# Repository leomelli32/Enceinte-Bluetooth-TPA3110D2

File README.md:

# Enceinte-Bluetooth-TPA3110D2
Conception d'une enceinte Bluetooth avec un amplificateur TPA3110D2 et un récepteur Bluetooth MH-M18.

## Caractéristiques techniques
- **Amplificateur :** Amplificateur TPA3110D2 de classe D (puissance de 2x15W limité à 8 pour les hauts-parleurs en stéréo)
- **Hauts parleurs :** Hauts parleurs d'une JBL Flip 3 (impédance d'entrée : 4 Ohms; puisance : 8 W)
- **Connectivité :** Récepteur Bluetooth MH-M18 géré par un diviseur de tension
- **Alimentation :** Pack Lithium-ion 3S (11.1V nominal) avec protection BMS et recharge USB-C via OT8228

## Paramétrages
- **Limitation de puissance :** Fonction PLIMIT de l'amplificateur, tension fixée à 2,19 V
- **Gain :** réglé à valeur minimale de 20 dB
- **Filtrage :** Filtre LC de sortie (15µH / 2.2µF) avec fréquence de coupure à 27 kHz.
- **PCB :** 4 couches : 1,2,4: GND; 3: Alimentation 12 V

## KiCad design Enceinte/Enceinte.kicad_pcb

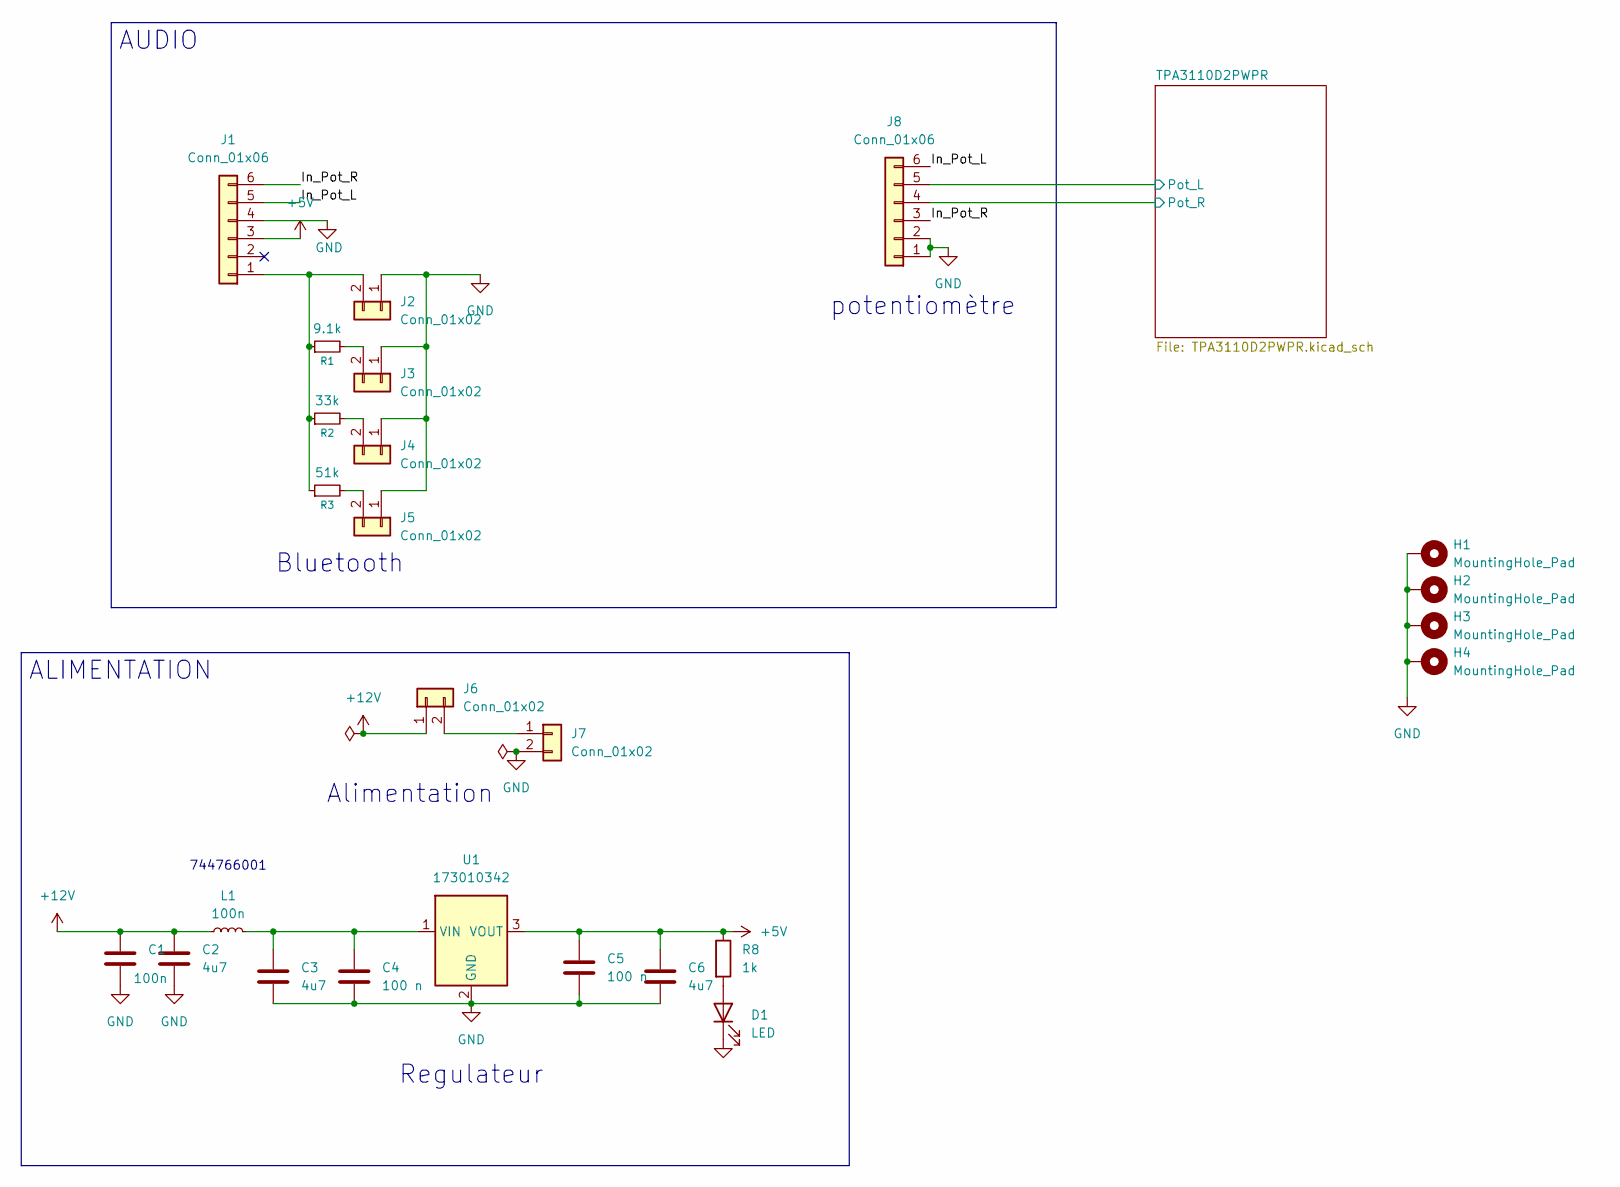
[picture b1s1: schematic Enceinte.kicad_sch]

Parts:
C1: 100n; C_0603_1608Metric
C2, C3, C6: 4u7; C_0603_1608Metric
C4, C5: 100 n; C_0603_1608Metric
D1: LED; LED_0603_1608Metric
H1, H2, H3, H4: MountingHole_Pad; MountingHole_2.5mm_Pad
J1, J8: Conn_01x06; JST_XH_B6B-XH-A_1x06_P2.50mm_Vertical
J2, J3, J4, J5, J6, J7: Conn_01x02; JST_XH_B2B-XH-A_1x02_P2.50mm_Vertical
L1: 100n; L_Wuerth_HCI-5040
R1: 9.1k; R_0603_1608Metric
R2: 33k; R_0603_1608Metric
R3: 51k; R_0603_1608Metric_Pad0.98x0.95mm_HandSolder
R8: 1k; R_0402_1005Metric
U1: 173010342; U_Wurth_MagIC-FDSM_173010x42

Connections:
+5V: C5.1, C6.1, J1.3, R8.1, U1.3 (VOUT)
+12V: C1.2, C2.1, J6.1, L1.1; also elsewhere on the board
/In_Pot_L: J1.5, J8.6
/In_Pot_R: J1.6, J8.3
/TPA3110D2PWPR/Pot_L: J8.5; also elsewhere on the board
/TPA3110D2PWPR/Pot_R: J8.4; also elsewhere on the board
GND: C1.1, C2.2, C3.2, C4.2, C5.2, C6.2, D1.1 (K), H1.1, H2.1, H3.1, H4.1, J1.4, J2.1, J3.1, J4.1, J5.1, J7.2, J8.1, J8.2, U1.2 (GND); also elsewhere on the board
unnamed: D1.2 (A), R8.2
unnamed: J1.1, J2.2, R1.1, R2.1, R3.1
unnamed: J3.2, R1.2
unnamed: J4.2, R2.2
unnamed: J5.2, R3.2
unnamed: J6.2, J7.1
unnamed: C3.1, C4.1, L1.2, U1.1 (VIN)

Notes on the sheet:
Regulateur
Alimentation
potentiomètre
Bluetooth
744766001
AUDIO
ALIMENTATION

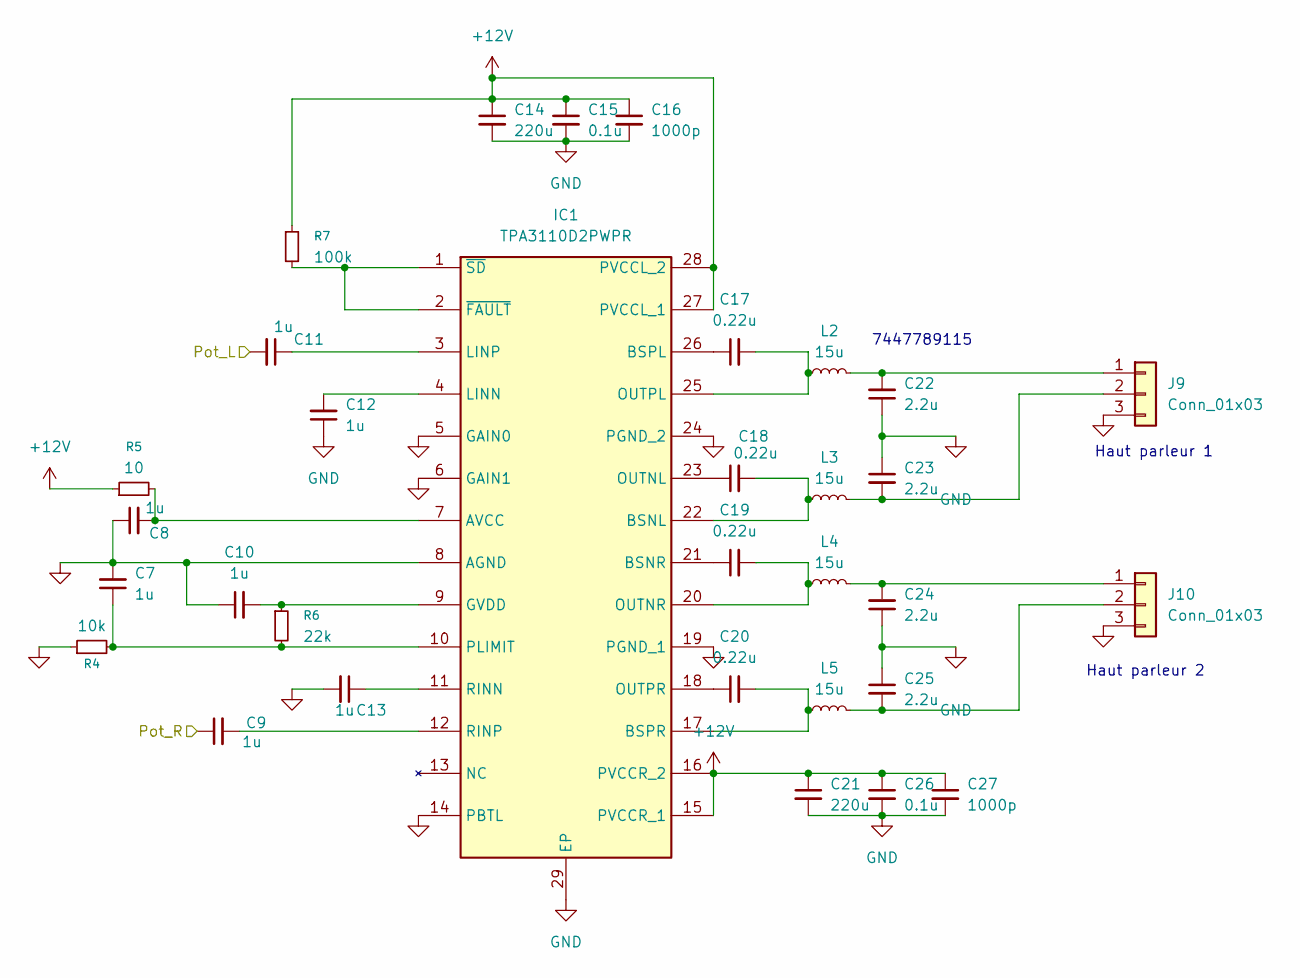
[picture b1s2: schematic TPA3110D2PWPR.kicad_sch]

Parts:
C7, C8, C9, C10, C11, C12, C13: 1u; C_0603_1608Metric
C14, C21: 220u; CP_Elec_6.3x7.7
C15, C26: 0.1u; C_0603_1608Metric
C16, C27: 1000p; C_0603_1608Metric
C17, C18, C19, C20: 0.22u; C_0603_1608Metric
C22, C23, C24, C25: 2.2u; C_0603_1608Metric
IC1: TPA3110D2PWPR; SOP65P640X120-29N; Mouser Part Number 595-TPA3110D2PWPR
J9, J10: Conn_01x03; JST_XH_B3B-XH-A_1x03_P2.50mm_Vertical
L2, L3, L4, L5: 15u; L_Wuerth_WE-PD-Typ-7345
R4: 10k; R_0603_1608Metric
R5: 10; R_0603_1608Metric
R6: 22k; R_0603_1608Metric
R7: 100k; R_0603_1608Metric

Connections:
+12V: C14.1, C15.1, C16.1, C21.1, C26.1, C27.1, IC1.15 (PVCCR_1), IC1.16 (PVCCR_2), IC1.27 (PVCCL_1), IC1.28 (PVCCL_2), R5.1, R7.1; also elsewhere on the board
/TPA3110D2PWPR/Pot_L: C11.2; also elsewhere on the board
/TPA3110D2PWPR/Pot_R: C9.1; also elsewhere on the board
GND: C7.2, C8.1, C10.1, C12.1, C13.2, C14.2, C15.2, C16.2, C21.2, C22.1, C23.1, C24.1, C25.1, C26.2, C27.2, IC1.5 (GAIN0), IC1.6 (GAIN1), IC1.8 (AGND), IC1.14 (PBTL), IC1.19 (PGND_1), IC1.24 (PGND_2), IC1.29 (EP), J9.3, J10.3, R4.1; also elsewhere on the board
unnamed: C8.2, IC1.7 (AVCC), R5.2
unnamed: C18.2, IC1.22 (BSNL), L3.1
unnamed: C19.1, IC1.21 (BSNR)
unnamed: C17.1, IC1.26 (BSPL)
unnamed: C20.2, IC1.17 (BSPR), L5.1
unnamed: C10.2, IC1.9 (GVDD), R6.1
unnamed: C12.2, IC1.4 (LINN)
unnamed: C11.1, IC1.3 (LINP)
unnamed: C18.1, IC1.23 (OUTNL)
unnamed: C19.2, IC1.20 (OUTNR), L4.1
unnamed: C17.2, IC1.25 (OUTPL), L2.1
unnamed: C20.1, IC1.18 (OUTPR)
unnamed: C7.1, IC1.10 (PLIMIT), R4.2, R6.2
unnamed: C13.1, IC1.11 (RINN)
unnamed: C9.2, IC1.12 (RINP)
unnamed: IC1.1 (~SD), IC1.2 (~FAULT), R7.2
unnamed: C22.2, J9.1, L2.2
unnamed: C23.2, J9.2, L3.2
unnamed: C24.2, J10.1, L4.2
unnamed: C25.2, J10.2, L5.2

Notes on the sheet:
Haut parleur 2
7447789115
Haut parleur 1

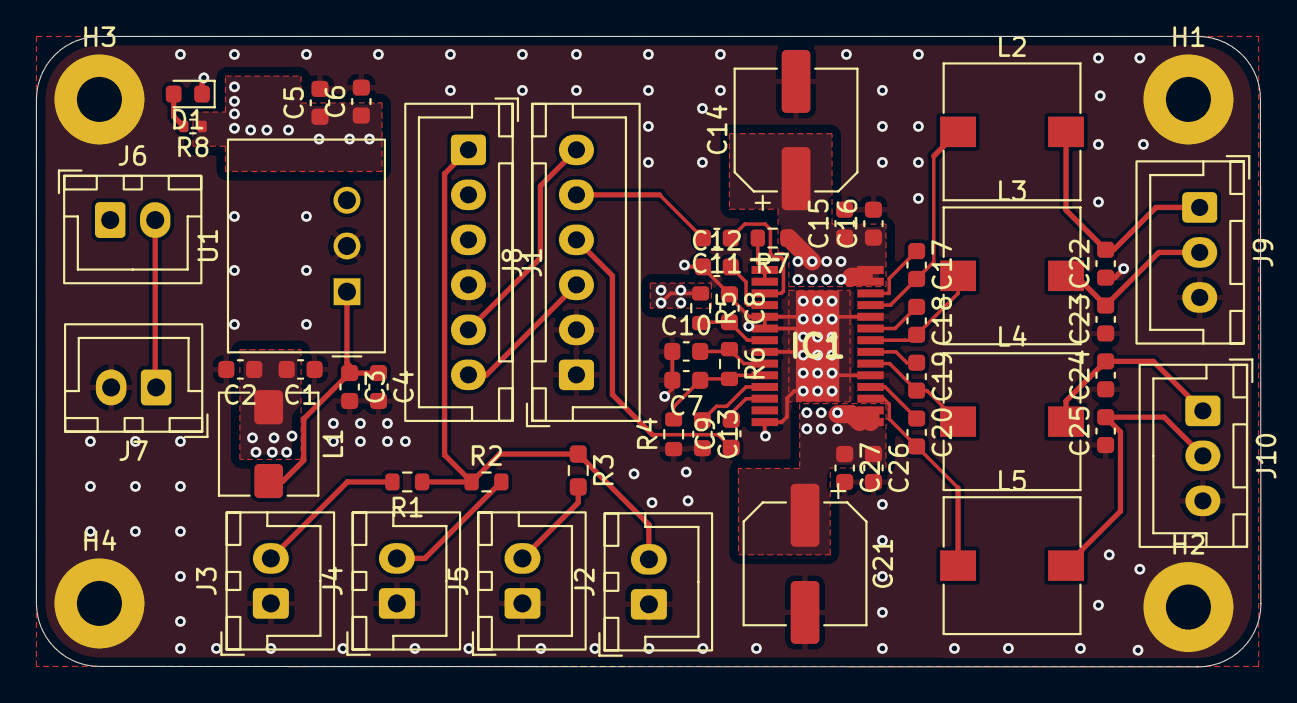
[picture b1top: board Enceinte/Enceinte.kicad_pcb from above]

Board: 4 copper layers, 68.0 x 35.0 mm, 57 parts (0 on the bottom side), 34 nets.

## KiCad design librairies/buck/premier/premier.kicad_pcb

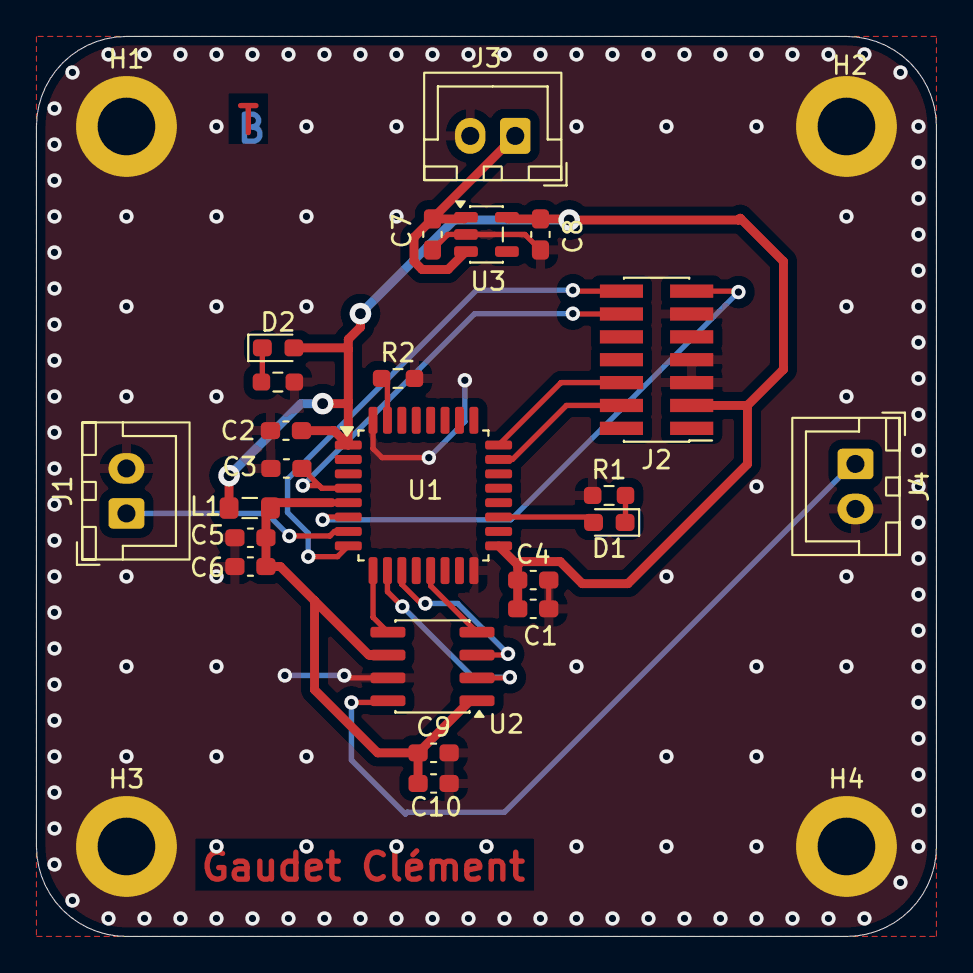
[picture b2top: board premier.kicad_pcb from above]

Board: 2 copper layers, 50.0 x 50.0 mm, 27 parts (0 on the bottom side), 19 nets.

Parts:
C1: 4u7; C_0603_1608Metric_Pad1.08x0.95mm_HandSolder
C2, C3, C4, C9: 100n; C_0603_1608Metric_Pad1.08x0.95mm_HandSolder
C5: 1u; C_0603_1608Metric_Pad1.08x0.95mm_HandSolder
C6, C10: 10n; C_0603_1608Metric_Pad1.08x0.95mm_HandSolder
C7, C8: 1uF; C_0603_1608Metric_Pad1.08x0.95mm_HandSolder
D1, D2: LED_Small; LED_0603_1608Metric_Pad1.05x0.95mm_HandSolder
H1, H2, H3, H4: MountingHole_Pad; MountingHole_3.2mm_M3_DIN965_Pad
J1, J3, J4: Conn_01x02; JST_XH_B2B-XH-A_1x02_P2.50mm_Vertical
J2: Conn_02x07_Odd_Even; PinHeader_2x07_P1.27mm_Vertical_SMD
L1: 39n; L_0805_2012Metric_Pad1.05x1.20mm_HandSolder
R1, R3: 1k; R_0603_1608Metric_Pad0.98x0.95mm_HandSolder
R2: 100k; R_0603_1608Metric_Pad0.98x0.95mm_HandSolder
U1: STM32L021K4Tx; LQFP-32_7x7mm_P0.8mm
U2: MCP4801; SOIC-8_3.9x4.9mm_P1.27mm
U3: BU33SD5WG-TR; SOT-23-5

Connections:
+3.3V: C1.1, C2.1, C4.1, C8.1, D2.2 (A), J2.3, L1.1, U1.1 (VDD), U1.17 (VDD), U3.5 (VOUT)
+3.3VA: C5.1, C6.1, C9.1, C10.1, L1.2, U1.5 (VDDA), U2.1 (Vdd), U2.6 (~SHDN)
+5V: C7.1, J3.1, U3.1 (VIN), U3.3 (~SHDN)
ADC_IN1: J1.1, U1.7 (PA1)
DAC_OUT: J4.1, U2.8 (Vout)
DAC_nCS: U1.10 (PA4), U2.2 (~CS)
DAC_nLDAC: U1.9 (PA3), U2.5 (~LDAC)
GND: C1.2, C2.2, C3.2, C4.2, C5.2, C6.2, C7.2, C8.2, C9.2, C10.2, H1.1, H2.1, H3.1, H4.1, J1.2, J2.5, J2.7, J2.11, J3.2, J4.2, R1.1, R2.2, R3.1, U1.16 (VSS), U1.32 (VSS), U2.7 (Vss), U3.2 (GND)
LED_STATUS: D1.2 (A), U1.19 (PA9)
NRST: C3.1, J2.12, U1.4 (NRST)
unnamed: D1.1 (K), R1.2
unnamed: D2.1 (K), R3.2
unnamed: R2.1, U1.31 (PB9)
SPI1_MOSI: U1.13 (PA7), U2.4 (SDI)
SPI1_SCK: U1.11 (PA5), U2.3 (SCK)
SWDCK: J2.6, U1.24 (PA14)
SWDIO: J2.4, U1.23 (PA13)
USART2_RX: J2.13, U1.6 (PA0)
USART2_TX: J2.14, U1.8 (PA2)

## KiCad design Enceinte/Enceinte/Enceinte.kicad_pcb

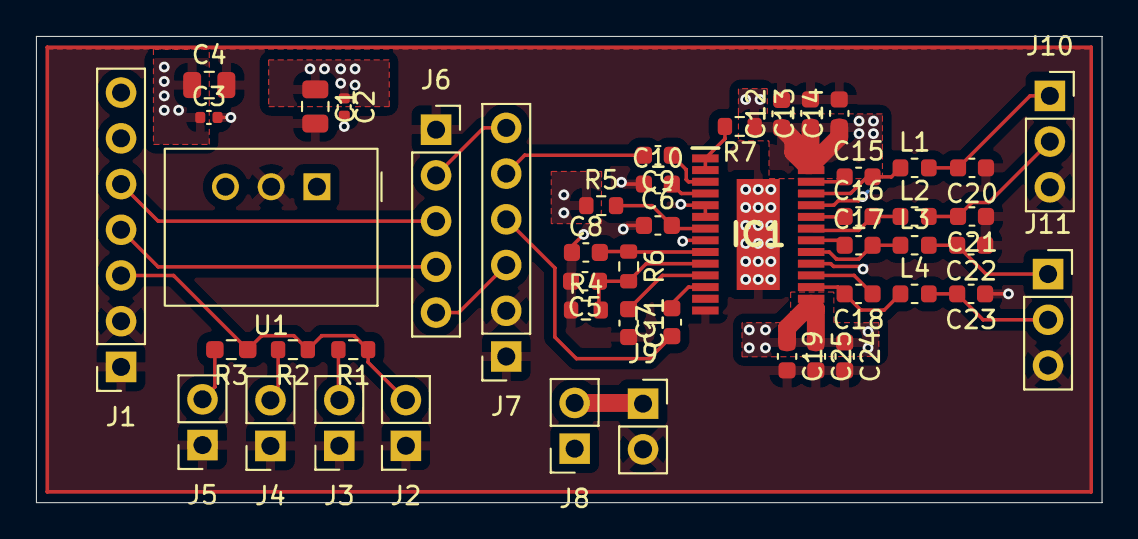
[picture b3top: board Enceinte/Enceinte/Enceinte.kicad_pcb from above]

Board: 4 copper layers, 59.2 x 25.9 mm, 49 parts (0 on the bottom side), 34 nets.

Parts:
C1, C4: 4u7; C_0805_2012Metric
C2, C3: 100 n; C_0402_1005Metric
C5, C6, C7, C8, C9, C10, C11: 1u; C_0603_1608Metric
C12, C19: 220u; C_0603_1608Metric
C13, C24: 0.1u; C_0603_1608Metric
C14, C25: 1000p; C_0603_1608Metric
C15, C16, C17, C18: 0.22u; C_0603_1608Metric
C20, C21, C22, C23: 2.2u; C_0603_1608Metric
IC1: TPA3110D2PWPR; SOP65P640X120-29N
J1: Conn_01x07; PinSocket_1x07_P2.54mm_Vertical
J2, J3, J4, J5, J8, J9: Conn_01x02; PinSocket_1x02_P2.54mm_Vertical
J6: Conn_01x05; PinSocket_1x05_P2.54mm_Vertical
J7: Conn_01x06; PinSocket_1x06_P2.54mm_Vertical
J10, J11: Conn_01x03; PinSocket_1x03_P2.54mm_Vertical
L1, L2, L3, L4: 15u; L_0603_1608Metric
R1: 9.1k; R_0603_1608Metric
R2: 33k; R_0603_1608Metric
R3: 51k; R_0603_1608Metric_Pad0.98x0.95mm_HandSolder
R4: 10k; R_0603_1608Metric
R5: 10; R_0603_1608Metric
R6: 22k; R_0603_1608Metric
R7: 100k; R_0603_1608Metric
U1: 173010342; U_Wurth_MagIC-FDSM_173010x42

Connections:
+5V: C3.1, C4.1, J1.7, U1.3 (VOUT)
+12V: C1.1, C2.1, C12.1, C13.1, C14.1, C19.1, C24.1, C25.1, IC1.15 (PVCCR_1), IC1.16 (PVCCR_2), IC1.27 (PVCCL_1), IC1.28 (PVCCL_2), J8.1, R5.1, R7.1, U1.1 (VIN)
/BT D: J1.4, J6.4
/BT G: J1.5, J6.3
/In_Pot_L: J6.2, J7.6
/In_Pot_R: J6.5, J7.3
/TPA3110D2PWPR/Pot_L: C9.2, J7.5
/TPA3110D2PWPR/Pot_R: C7.1, J7.4
GND: C1.2, C2.2, C3.2, C4.2, C5.2, C6.1, C8.1, C10.1, C11.2, C12.2, C13.2, C14.2, C19.2, C20.1, C21.1, C22.1, C23.1, C24.2, C25.2, IC1.5 (GAIN0), IC1.6 (GAIN1), IC1.8 (AGND), IC1.14 (PBTL), IC1.19 (PGND_1), IC1.24 (PGND_2), IC1.29 (EP), J1.1, J1.2, J2.1, J3.1, J4.1, J5.1, J6.1, J7.1, J7.2, J9.2, J10.3, J11.3, R4.1, U1.2 (GND)
unnamed: C6.2, IC1.7 (AVCC), R5.2
unnamed: C16.2, IC1.22 (BSNL), L2.1
unnamed: C17.1, IC1.21 (BSNR)
unnamed: C15.1, IC1.26 (BSPL)
unnamed: C18.2, IC1.17 (BSPR), L4.1
unnamed: C8.2, IC1.9 (GVDD), R6.1
unnamed: C10.2, IC1.4 (LINN)
unnamed: C9.1, IC1.3 (LINP)
unnamed: C16.1, IC1.23 (OUTNL)
unnamed: C17.2, IC1.20 (OUTNR), L3.1
unnamed: C15.2, IC1.25 (OUTPL), L1.1
unnamed: C18.1, IC1.18 (OUTPR)
unnamed: C5.1, IC1.10 (PLIMIT), R4.2, R6.2
unnamed: C11.1, IC1.11 (RINN)
unnamed: C7.2, IC1.12 (RINP)
unnamed: IC1.1 (~SD), IC1.2 (~FAULT), R7.2
unnamed: J1.3, J2.2, R1.1, R2.1, R3.1
unnamed: J3.2, R1.2
unnamed: J4.2, R2.2
unnamed: J5.2, R3.2
unnamed: J8.2, J9.1
unnamed: C20.2, J10.1, L1.2
unnamed: C21.2, J10.2, L2.2
unnamed: C22.2, J11.1, L3.2
unnamed: C23.2, J11.2, L4.2

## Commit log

2026-03-11 Ajout compte-rendu
2026-03-12 Importation du kicad
2026-03-12 Routage terminé
2026-03-14 Changement régulateur de tension
2026-03-16 correction des bordures
2026-03-16 des changements sont à faire
2026-03-20 doc latex
2026-03-25 librairies
2026-03-25 nouvelles inductances
2026-03-30 indu Wurth
